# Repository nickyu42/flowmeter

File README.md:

<div align="center">
  <h1>Energy Harvesting Flow Meter</h1>

</div>

## About

This repository contains the hardware design and software for a wireless, energy harvesting flow meter. This is an inexpensive water consumption sensor that does not require external power or cables to transmit data. It uses a turbine as power supply, the power supply is also used as input to estimate water consumption.

This project was done as part of the Advanced Practical IoT and Seminar course given at the Delft University of Technology. If you are interested in the research, an accompanying [paper](paper.pdf) is available in this repository.

## Repository Structure

This project is split up into different components:

- `pcb`  
    KiCAD files for the prototype
- `analysis.ipynb`  
    Notebook containing all plots and analysis from the dataset in `data`
- `gateway`
  - Firmware for the receiver ESP32
  - UART-to-MQTT script, parses the serial data from the receiver ESP and publishes that to a MQTT server
  - All code for the web dashboard for tracking water usage
- `stm32f4_firmware`  
  Code for the testing setup with a STM32, based around [MBed OS](https://os.mbed.com/mbed-os/).
- `esp32_firmware`  
  ESP32 firmware for the prototype, transmits the estimated water flow rate and power metrics via ESP-NOW to the receiver. Built using [FreeRTOS](https://www.freertos.org/) and [ESP-IDF](https://docs.espressif.com/projects/esp-idf/en/latest/esp32/index.html).

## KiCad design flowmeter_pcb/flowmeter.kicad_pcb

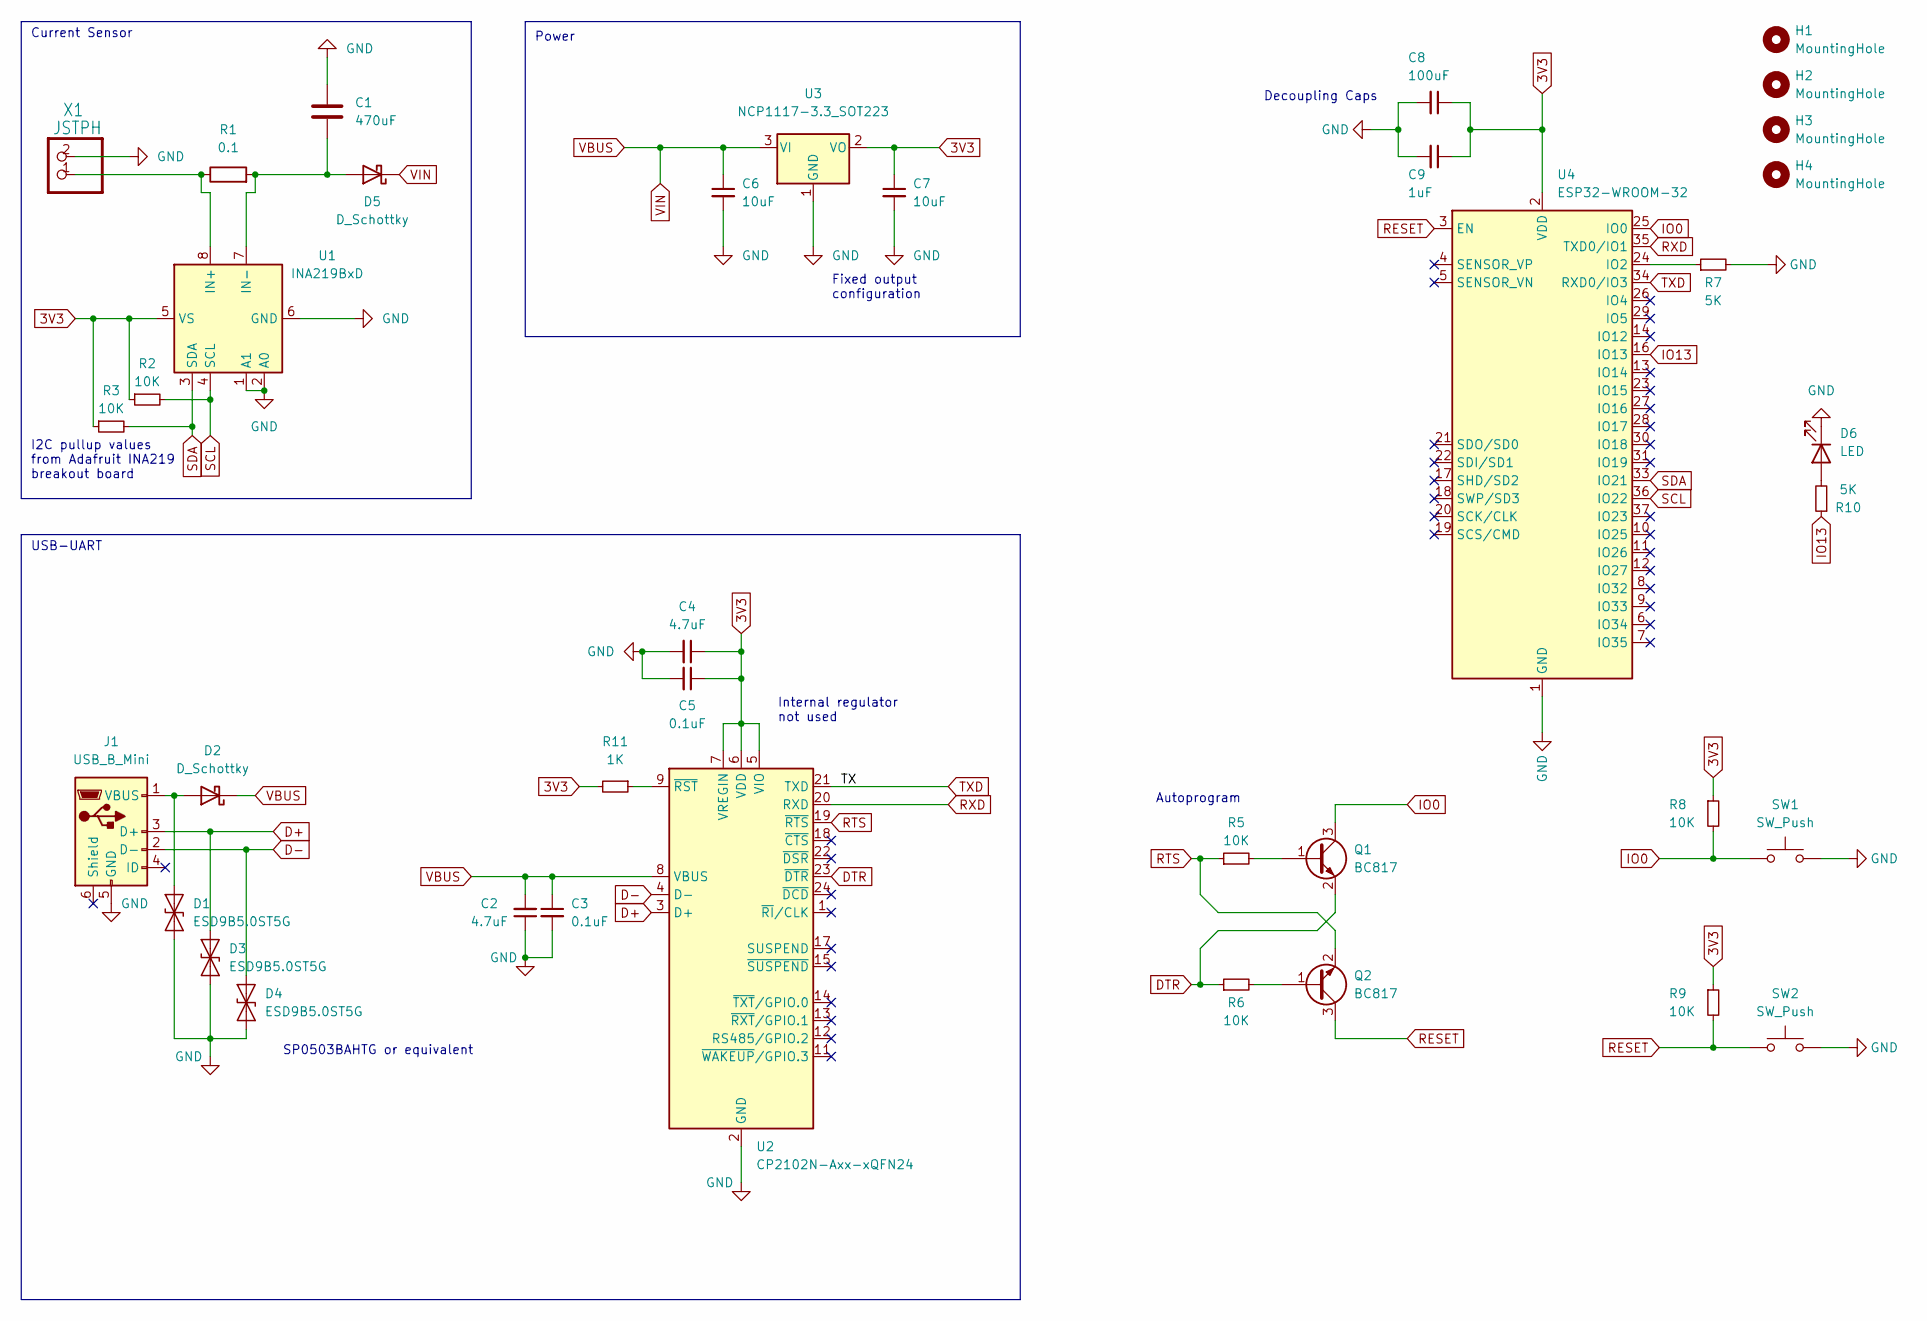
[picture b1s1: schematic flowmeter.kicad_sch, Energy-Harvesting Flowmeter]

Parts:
C1: 470uF; D_SOD-123
C2, C4: 4.7uF; C_1206_3216Metric_Pad1.33x1.80mm_HandSolder
C3, C5: 0.1uF; C_1206_3216Metric_Pad1.33x1.80mm_HandSolder
C6, C7: 10uF; C_1206_3216Metric_Pad1.33x1.80mm_HandSolder
C8: 100uF; C_1206_3216Metric_Pad1.33x1.80mm_HandSolder
C9: 1uF; C_1206_3216Metric_Pad1.33x1.80mm_HandSolder
D1, D3, D4: ESD9B5.0ST5G; D_SOD-923
D2, D5: D_Schottky; D_SOD-123
D6: LED; LED_1206_3216Metric_Pad1.42x1.75mm_HandSolder
H1, H2, H3, H4: MountingHole; MountingHole_2.2mm_M2_DIN965
J1: USB_B_Mini; USB_Micro-B_Molex-105017-0001
Q1, Q2: BC817; SOT-23
R1: 0.1; R_2512_6332Metric_Pad1.40x3.35mm_HandSolder
R2, R3, R5, R6, R8, R9: 10K; R_1206_3216Metric_Pad1.30x1.75mm_HandSolder
R7, R10: 5K; R_1206_3216Metric_Pad1.30x1.75mm_HandSolder
R11: 1K; R_1206_3216Metric_Pad1.30x1.75mm_HandSolder
SW1, SW2: SW_Push; SW_Push_1P1T_NO_CK_KMR2
U1: INA219BxD; SOIC-8_3.9x4.9mm_P1.27mm
U2: CP2102N-Axx-xQFN24; QFN-24-1EP_4x4mm_P0.5mm_EP2.6x2.6mm
U3: NCP1117-3.3_SOT223; SOT-223-3_TabPin2
U4: ESP32-WROOM-32
X1: JSTPH; JST_PH_S2B-PH-SM4-TB_1x02-1MP_P2.00mm_Horizontal

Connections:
3V3: C4.1, C5.1, C7.1, C8.1, C9.1, R2.1, R3.1, R8.1, R9.1, R11.2, U1.5 (VS), U2.5 (VIO), U2.6 (VDD), U2.7 (VREGIN), U3.2 (VO), U4.2 (VDD)
D+: D3.2 (A2), J1.3 (D+), U2.3 (D+)
D-: D4.2 (A2), J1.2 (D-), U2.4 (D-)
DTR: Q1.2 (E), R6.1, U2.23 (~DTR)
GND: C1.2, C2.1, C3.2, C4.2, C5.2, C6.2, C7.2, C8.2, C9.2, D1.1 (A1), D3.1 (A1), D4.1 (A1), D6.1 (K), J1.5 (GND), R7.2, SW1.2, SW2.2, U1.1 (A1), U1.2 (A0), U1.6 (GND), U2.2 (GND), U2.25 (GND), U3.1 (GND), U4.1 (GND), U4.15 (GND), U4.38 (GND), U4.39 (GND), X1.2
IO0: Q1.3 (C), R8.2, SW1.1, U4.25 (IO0)
IO13: R10.1, U4.16 (IO13)
unnamed: C1.1, D5.2 (A), R1.2, U1.7 (IN-)
unnamed: D1.2 (A2), D2.2 (A), J1.1 (VBUS)
unnamed: Q1.1 (B), R5.2
unnamed: Q2.1 (B), R6.2
unnamed: R7.1, U4.24 (IO2)
unnamed: D6.2 (A), R10.2
unnamed: R11.1, U2.9 (~RST)
unnamed: R1.1, U1.8 (IN+), X1.1
RESET: Q2.3 (C), R9.2, SW2.1, U4.3 (EN)
RTS: Q2.2 (E), R5.1, U2.19 (~RTS)
RXD: U2.20 (RXD), U4.35 (TXD0/IO1)
SCL: R2.2, U1.4 (SCL), U4.36 (IO22)
SDA: R3.2, U1.3 (SDA), U4.33 (IO21)
TXD: U2.21 (TXD), U4.34 (RXD0/IO3)
VBUS: C2.2, C3.1, C6.1, D2.1 (K), D5.1 (K), U2.8 (VBUS), U3.3 (VI)

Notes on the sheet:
Power
USB-UART
Autoprogram
Decoupling Caps
I2C pullup values from Adafruit INA219 breakout board
SP0503BAHTG or equivalent
Internal regulator not used
Fixed output configuration
Current Sensor

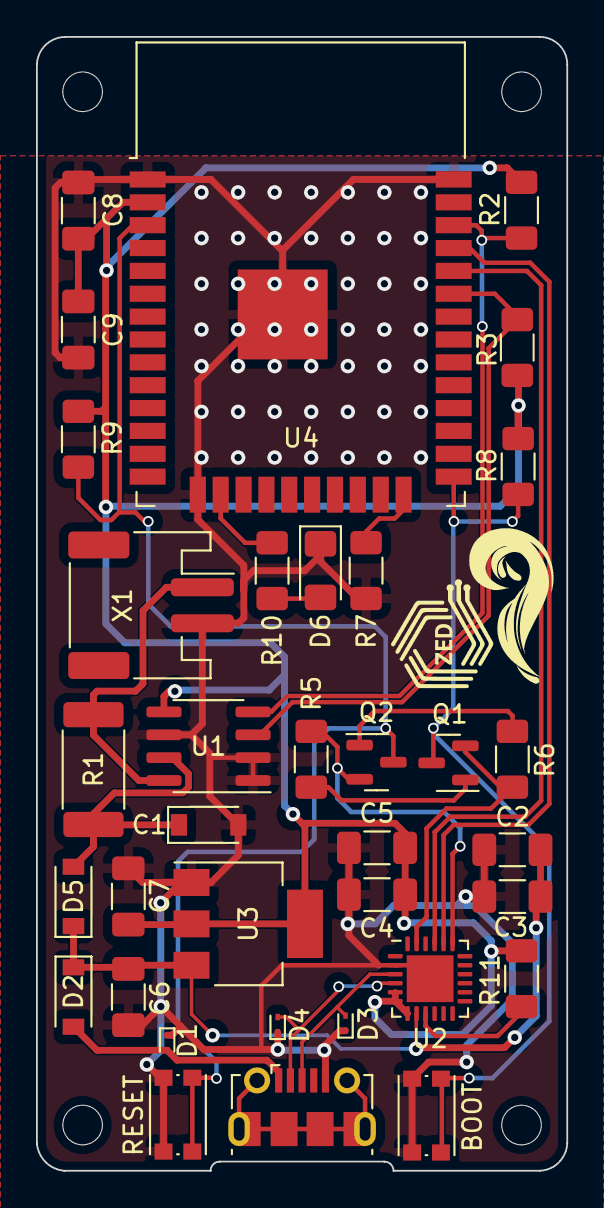
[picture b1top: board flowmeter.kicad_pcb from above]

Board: 2 copper layers, 29.5 x 63.0 mm, 39 parts (0 on the bottom side), 22 nets.

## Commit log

2022-09-26 initial
2022-10-20 Basic INA219
2022-10-24 Add csv capture and analysis notebook
2022-10-27 Update analysis
2022-11-01 change flowrate metric to power
2022-11-01 rewrite event loop to use interrupts
2022-11-04 new data
2022-11-30 Add cumulative
2022-11-30 Add all
2022-11-30 Add pcb
2022-12-07 Cleanup
2022-12-07 Add paper to the repo
